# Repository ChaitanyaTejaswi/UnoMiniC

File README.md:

# UnoMiniC

UnoMiniC is a compact, USB-C–powered Arduino Uno-compatible board designed for modern embedded development. It features the ATmega328PB and ATmega16U2 for reliable USB-to-serial communication with auto-reset support.

Created to address the size and USB limitations of traditional Arduino boards, UnoMiniC offers a Pico-sized design with breakouts for VIN, ICSP, and DTR reset. The board is powered and programmed through a USB C interface; a VIN pin breakout is provided in case it has to be ran on a battery pack. ICSP headers (as test points) is provided for  both  ATmega16U2  and  ATmega328PB.  On-board  auto  reset  is  configured  to  reset  the microcontroller  to programming  mode  when programming with  the  USB interface.

## Software Reqiurement  

**KiCAD**: Platform used to design the schematic and PCB layout.  
**Atmel FLIP**: Used for updating the atmega16U2 with USB interface firmware.  
**Arduino IDE/VSC**: Programming and testing the final board.

## Board Setup

### Flash USB-to-serial firmware in DFU mode

The firmware for ATmega16U2 is located inside `ArduinoCore-avr/firmwares/atmegaxxu2/arduino-usbserial/`.
Use the `Arduino-COMBINED-dfu-usbserial-atmega16u2-Uno-Rev3.hex` hex file.

> [!IMPORTANT]  
> Make sure that the fuses are set to utilise the external 16 MHz crystal oscillator and disable ```Divide clock by 8 internally``` by setting the ```CLKDIV8 bit``` in the CLKPR – Clock Prescale Register.

### Program the ATmega16U2 chip with USB-Serial firmware

#### Using dfu-programmer (macOS/Linux)

* Download **dfu-programmer** from the [GitHub repository](https://github.com/dfu-programmer/dfu-programmer/releases) or install the dfu-programmer package using a package manager like [homebrew](https://brew.sh/index) (macOS) or [apt-get](https://manpages.ubuntu.com/manpages/kinetic/en/man8/apt-get.8.html) (Ubuntu).

* Connect the board to your computer.

* Set the ATmega16U2 to DFU mode.
   - Short the RST Test Pad to the nearest available GND pin

* Open Terminal.

* Erase the memory.
   ```
   dfu-programmer atmega16u2 erase
   ```
* Flash the firmware.
   ```
   dfu-programmer atmega16u2 ./ArduinoCore-avr/firmwares/atmegaxxu2/arduino-usbserial/Arduino-COMBINED-dfu-usbserial-atmega16u2-Uno-Rev3.hex
   ```
* Disconnect and reconnect the board to your computer.

#### Using FLIP (Windows)

* Download and install [Flip](https://www.microchip.com/en-us/development-tool/flip).

* Connect the board to your computer.

* Set the ATmega16U2 to DFU mode.
   - Short the RST Test Pad to the nearest available GND pin

* Open FLIP.

* Connect to the chip by clicking the cable button, select USB, then click open.

* In the Menu, click Device > Select > ATmega16U2.

* Click File > Load HEX file

* Navigate to `ArduinoCore-avr/firmwares/atmegaxxu2/arduino-usbserial/`, select `Arduino-COMBINED-dfu-usbserial-atmega16u2-Uno-Rev3.hex` and then click OK.

* Click on the `Program Target Device Memory` button.

* The firmware will be flashed, and `Programming done` message should be displayed in the bottom-left corner.

### Download MiniCore 
#### Boards Manager Installation
This installation method requires Arduino IDE version 1.8.0 or greater.

* Open the Arduino IDE.

* Open the **File > Preferences** menu item.

* Enter the following URL in **Additional Boards Manager URLs**:

    ```
    https://mcudude.github.io/MiniCore/package_MCUdude_MiniCore_index.json
    ```

* Open the **Tools > Board > Boards Manager...** menu item.

* Wait for the platform indexes to finish downloading.

* Scroll down until you see the **MiniCore** entry and click on it.

* Click **Install**.

* After installation is complete close the **Boards Manager** window.

#### Manual Installation
Click on the "Download ZIP" button in the upper right corner. Extract the ZIP file, and move the extracted folder to the location "**~/Documents/Arduino/hardware**". Create the "hardware" folder if it doesn't exist.
Open Arduino IDE, and a new category in the boards menu called "MiniCore" will show up.

#### Arduino CLI Installation
Run the following command in a terminal:

```
arduino-cli core install MiniCore:avr --additional-urls https://mcudude.github.io/MiniCore/package_MCUdude_MiniCore_index.json
```

## Setting up the board for the first time

> [!NOTE]
> You will need an ICSP Programmer for this step as we need to flash the URBoot bootloader on the ATmega328PB.

* Under the boards menu: select **MiniCore > ATmega328**.

* Select Clock to **External 16MHZ** and Variant to **328PB**.

* Connect your ICSP programmer to the ICSP header on the back of the board.  

* Under **Tools**, select correct programmer and hit **Burn bootloader**.

The board is now setup and the USB C port can be used for serial programming just like any other microcontroller development board.

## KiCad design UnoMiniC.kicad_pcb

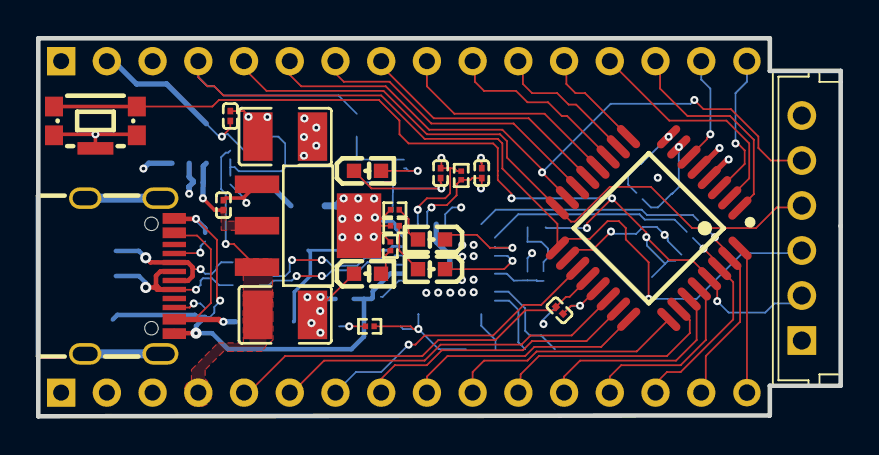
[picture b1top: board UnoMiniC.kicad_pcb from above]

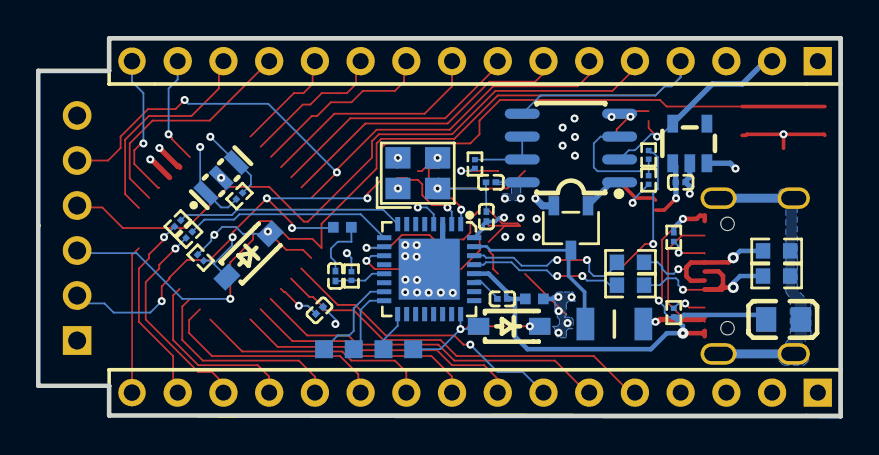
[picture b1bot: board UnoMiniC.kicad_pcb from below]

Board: 4 copper layers, 44.6 x 21.0 mm, 59 parts (34 on the bottom side), 62 nets.

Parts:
C1, C4, C11, C12, C13: 0.1u; C0201
C2, C3: 47uF; C1210
C5: 2.2u; C0201
C6, C9, C10: 1u; C0201
C7, C8: 10p; C0201
D1, D2: 1N4148WQ-13-F; SOD-123_L2.7-W1.6-LS3.7-RD-1
F1: PTS12066V050; FUSC3216X68N
J2: HDR-M-2.54_2x3; CONN-TH_6P-P2.50_JST_B6B-EH-LF-SN
J3, J4: HDR-M-2.54_1x16; HDR-M-2.54_1X16
L1: 220Ω; L0805
LED1, LED2, LED3, LED4: HSMQ-C191; LED-SMD_L1.6-W0.8-R-RD
Pad_gge82640: Pad_gge82640
Pad_gge82664: Pad_gge82664
Pad_gge82688: Pad_gge82688
Pad_gge82712: Pad_gge82712
Q1: DMG3415UQ-7; SOT-23-3_L2.9-W1.6-P1.90-LS2.8-BR
R1, R2, R13, R14: 510; R0201
R3, R4, R6, R17: 10k; R0201
R5, R16: 1M; R0201
R7, R8: 22R; R0603
R9, R12: 5.1k; R0201
R10, R11: CG0603MLC-05E; R0603
R15, R18: 0; RESC1005X37N
R19, R20, R21: 1k; R0201
SW1: KMR221GLFS; KEY-SMD_KMR2XXGXXX
U1: LM358DR; SOIC-8_L5.0-W4.0-P1.27-LS6.0-BL
U2: LD1117S33CTR; SOT-223-4_L6.5-W3.5-P2.30-LS7.0-BR
U3: LP2985IM5X-3.3; SOT-23-5_L2.9-W1.6-P0.95-LS2.8-BR
U4: ATMEGA16U2-MU; QFN-32_L5.0-W5.0-P0.50-BL-EP3.4
U5: ATMEGA328PB-AU; TQFP-32_L7.0-W7.0-P0.80-LS9.0-BL
USBC1: TYPE-C-31-M-12; USB-C_SMD-TYPE-C-31-M-12
X1: ABM8G-16.000MHZ-4Y-T3; CRYSTAL-SMD_4P-L3.2-W2.5-BL
X2: 16MHz; OSC-SMD_3P-L3.2-W1.3-P1.20-L

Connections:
3V3_LDO: C5.2, J4.2, U1.2, U3.5
5V_LDO: C1.1, C3.2, C4.2, C6.2, C9.2, C11.2, D1.1, D2.1, J2.1, J3.1, J4.1, Q1.2, R2.2, R6.2, R13.1, R14.1, R17.2, U1.8, U2.2, U2.4, U3.1, U3.3, U4.4, U4.32, U5.4, U5.18
ARD_AN0: J3.8, U5.23
ARD_AN1: J3.9, U5.24
ARD_AN2: J3.10, U5.25
ARD_AN3: J3.11, U5.26
ARD_AN4/SDA: J3.12, U5.27
ARD_AN5/SCL: J3.13, U5.28
ARD_DIG0: J3.14, R20.2, U5.30
ARD_DIG1: J3.15, R21.2, U5.31
ARD_DIG2: J3.16, U5.32
ARD_DIG3: J4.14, U5.1
ARD_DIG4: J4.13, U5.2
ARD_DIG5: J4.12, U5.9
ARD_DIG6: J4.11, U5.10
ARD_DIG7: J4.10, U5.11
ARD_DIG8: J4.9, U5.12
ARD_DIG9: J4.8, U5.13
ARD_DIG10/SPI_SS: J4.7, U5.14
ARD_DIG11/SPI_MOSI: J2.5, J4.6, U5.15
ARD_DIG12/SPI_MISO: J2.4, J4.5, U5.16
ARD_DIG13/SPI_SCK: J2.3, J4.4, U1.5, U5.17
ARD_RESET: D2.2, J2.2, R17.1, R18.2, SW1.3, SW1.4, U5.29
AREF: C12.2, J3.5, U5.20
DTR: C13.2, R19.2, U4.13
GND: C1.2, C2.1, C3.1, C4.1, C5.1, C6.1, C7.2, C8.2, C9.1, C11.1, C12.1, J2.6, J3.2, J3.3, J4.3, LED1.2, LED2.2, R4.1, R15.1, R19.1, SW1.1, SW1.2, SW1.5, U1.4, U2.1, U3.2, U4.3, U4.33, U5.5, U5.21, X1.2, X1.4, X2.2
ICSP_MISO: Pad_gge82688.3, U4.17
ICSP_MOSI: Pad_gge82664.2, U4.16
ICSP_SCK: Pad_gge82640.1, U4.15
LED2_1: LED2.1, R2.1
LED3_1: LED3.1, R13.2
LED4_1: LED4.1, R14.2
PE0: J4.16, U5.3
PE1: J4.15, U5.6
PE2: J3.7, U5.19
PE3: J3.6, U5.22
R1_2: LED1.1, R1.2
R18_1: C13.1, R18.1
SERIALRX: R20.1, U4.9
SERIALTX: R21.1, U4.8
SLD: L1.2, R10.1, R11.1, USBC1.0, USBC1.1, USBC1.2, USBC1.3
U1_1: Q1.1, U1.1
U1_3: R3.1, R4.2, U1.3
U1_7: R1.1, U1.6, U1.7
U4_1: C7.1, R5.2, U4.1, X1.3
U4_2: C8.1, R5.1, U4.2, X1.1
U4_10: LED3.2, U4.10
U4_11: LED4.2, U4.11
U4_24: D1.2, Pad_gge82712.4, R6.1, U4.24
U4_27: C10.1, U4.27
USBC1_A5: R12.2, USBC1.A5
USBC1_B5: R9.2, USBC1.B5
USBC1_B6: R8.1, R10.2, USBC1.A6, USBC1.B6
USBC1_B7: R7.1, R11.2, USBC1.A7, USBC1.B7
USBGND: C10.2, L1.1, R9.1, R12.1, R15.2, U4.28, USBC1.A1, USBC1.A12, USBC1.B1, USBC1.B12
USBV: F1.1, USBC1.A4, USBC1.A9, USBC1.B4, USBC1.B9
USBVCC: F1.2, Q1.3, U4.31
USB_D+: R8.2, U4.29
USB_D-: R7.2, U4.30
VIN: C2.2, J3.4, R3.2, U2.3
X2_1: R16.2, U5.7, X2.1
X2_3: R16.1, U5.8, X2.3

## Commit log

2025-04-16 Updated Documentation
